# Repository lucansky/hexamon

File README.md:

# Hexamon.io - modular wireless beehive weighting system

Beehive monitoring - solves data acquisition from load cells placed under the beehives, data transport to server and data visualization for user.

## Architecture overview
### Master
Master unit consist of a Raspberry Pi with a CAN shield with RJ12 connector.
CAN shield is a board with SPI [MCP2515 CAN controller](http://ww1.microchip.com/downloads/en/DeviceDoc/21801d.pdf) and [SN65HVD23x](http://www.ti.com/lit/ds/symlink/sn65hvd230.pdf) CAN transceiver.

### Power management
The system is powered through a [18V solar panel](https://www.i4wifi.cz/Solarni-panely-1/Solarni-panely/Solarni-panel-GWL-Sunny-Poly-20-Wp-36-cells-MPPT-18V.html), charging [12V battery](https://www.gme.cz/oloveny-akumulator-shimastu-npg7-2-12-12v-7-2ah).
Enclosure with master unit has power management board for charging circuit with under-voltage protection, as well as 5V USB ports for output.

20W solar panel was selected for a prototype, due to it's ability to supply sufficient energy even during cloudy days for a Raspberry Pi.

### Bus unit
Under each beehive, assuming that whole chain of beehives is no longer than 100m, is placed platform with load cells for measuring the weight and bus unit in an enclosure. First beehive in chain contains Master and Bus unit at once.

Bus unit has STM32F042F6P6 in an TSSOP20 package with CAN transceiver and two RJ12 connectors for daisy-chaining to other bus units, as well as two holders for HX711 breakout boards. [Converters boards](https://www.aliexpress.com/item/10pcs-HX711-Weighing-Sensor-Dual-Channel-24-Bit-Precision-A-D-Module-Pressure-Sensor/32656264280.html) can be purchased through eBay or AliExpress.

Schematics & board design can be found in _boards_ directory.

### Weight acquisition
As an ADC with differential amplifier was selected chip HX711 integrated on a beakout board with all the necessary electronics around.

## Hardware
### Platform
Simple two-rail platform consists of three components:
* Load cell Zemic L6E or equivalent
* 2x Spacer
* 50x50mm 45cm L profile with drilled holes to match load-cell

Middle bars may be optional, depending on the situation:
* 2x Rectangle aluminium profile 25x15x3mm 25cm
* 2x Rectangle aluminium profile 25x30x3mm 25cm
These fit perfectly together. By drilling holes, pitch can be adjusted.

As the platform was not part of the project assignment, [contact me](mailto:adamlucansky@gmail.com) in case of interest.

### Load cells
During development, [Zemic L6E](https://www.zemiceurope.com/media/Documentation/L6E_Datasheet.pdf) were selected. For deployment, [L6G](https://www.zemiceurope.com/media/Documentation/L6G_Datasheet.pdf) are used. 

## Modularity
Several beehives can be chained together with a telephone cable with RJ12 jack through Bus unit under beehive, while master unit is sending captured data wirelessly to server through WiFi (3G/GSM modem option was tested and implemented, but is not further described, wvdial utility & whole ecosystem of linux drivers for modems make it diffucult for set-up).

## Software
### Master unit
Raspberry Pi 3 running Raspbian system, with an SPI overlay, provides can0 network interface which can be easily interfaced through linux socket. [Main program](https://github.com/lucansky/hexamond) is written in Haskell and is basically flipping frames received on CAN bus to HTTP requests to webservers where the data are further processed.

### Bus unit
[STM32F042](http://www.st.com/en/microcontrollers/stm32f0x2.html) MCU on board has 32kB of Flash memory and 6kB SRAM. Ivory language has been selected for generation of the C code, and Ivory framework as a hardware abstraction layer, message passing and RTOS interaction. Therefore whole project is 100% Haskell except the web. Firmware can be found [HERE](https://github.com/lucansky/hexamon-firmware).

### Web
Web interface provides charts for all sensors connected to the network as well as dashboard defined by user for aggregated statistics. Each setup requires separate instance of the web with database. Source code can be found [HERE](https://github.com/lucansky/hexamon-web)

# Results
System is deployed on a few beehives, needs a bit more tweaking (grounding of the metal platform with beehives, as interference is generated during thunderstorm) and better cable management.

__candump__ can be seed on monitor of the laptop of the deployment set. Battery is already charging from solar panel.

# Future work
Due to over-engineered solution, next iteration will be with [SIGFOX](https://en.wikipedia.org/wiki/Sigfox) - one module per beehive (just load cell cable connected to small box, 2xAA battery, optionally DS18B20 temperature sensor). Currently waiting for a [better signal coverage in Slovakia](http://www.simplecell.sk/pages/technologia_sigfox/), which is the reason SIGFOX was not considered from the beginning.

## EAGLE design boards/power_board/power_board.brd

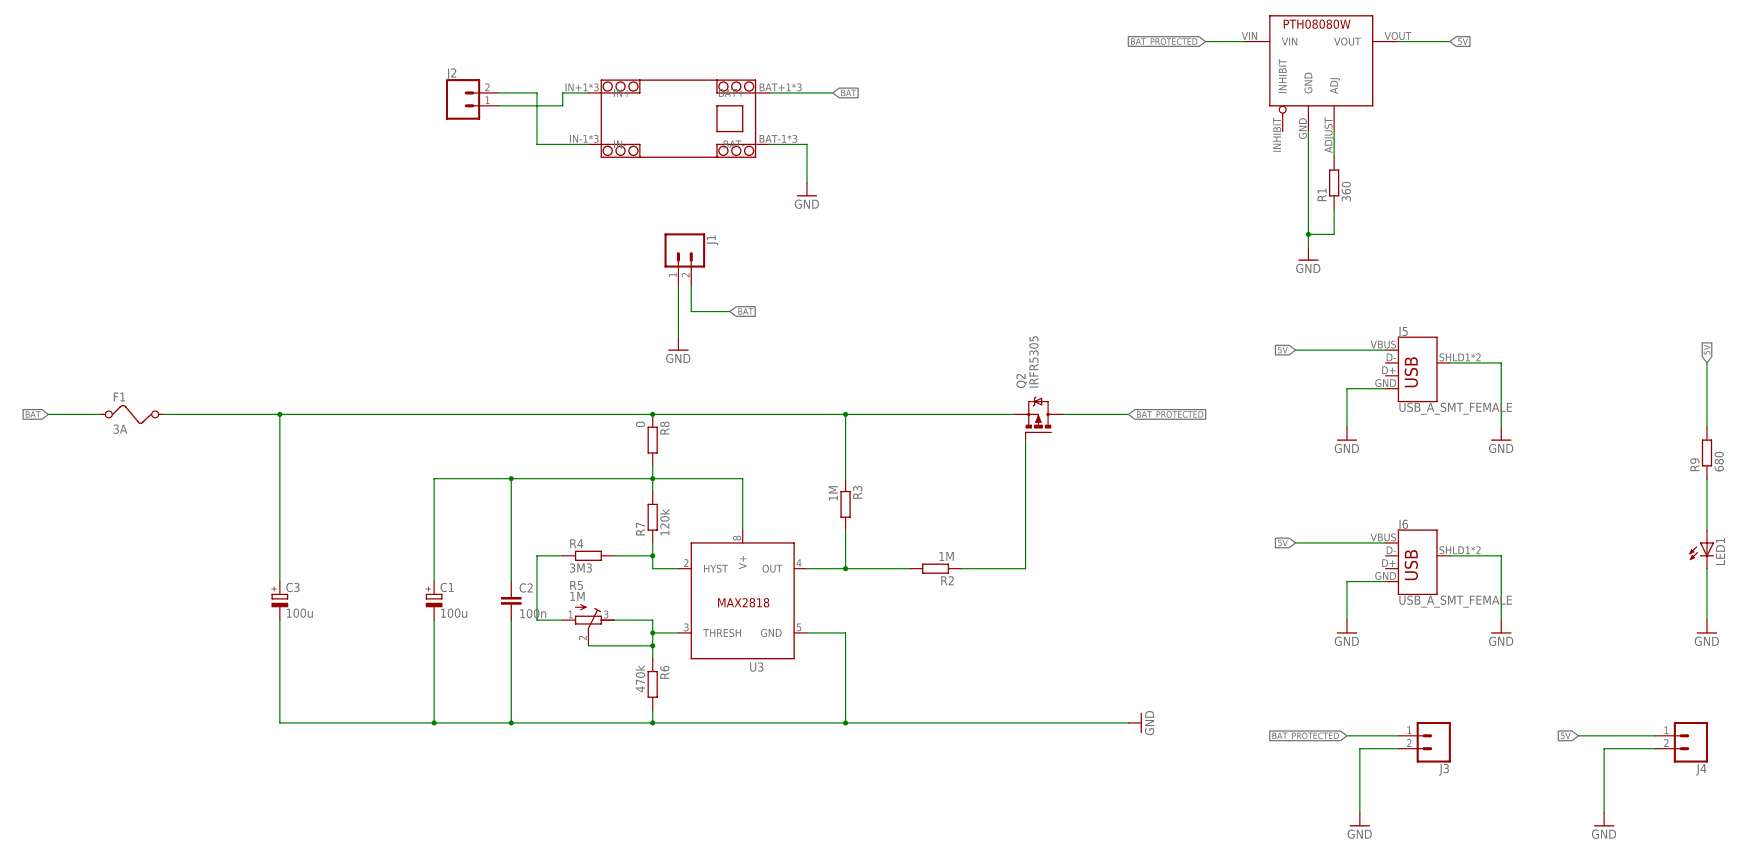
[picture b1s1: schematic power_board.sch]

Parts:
C1, C3: 100u; E3,5-8
C2: 100n; C1206
F1: 3A; FUSE
J1, J2, J4: CONN_025MM; SCREWTERMINAL-5MM-2
J3: CONN_02; 1X02
J5, J6: USB_A_SMT_FEMALE; USB-A-S-SILK-FEMALE
LED1: LED3MM
Q2: IRFR5305; D-PAK_TO252AA
R1: 360; R1206
R2, R3: 1M; R1206
R4: 3M3; R1206
R5: 1M; RTRIM64Y
R6: 470k; R1206
R7: 120k; R1206
R8: 0; R1206
R9: 680; R1206
U1: YZXSTUDIO_SOLARCHARGERDEFAULT; YZXSTUDIO_SOLARCHARGER
U2: PTH08080WPTH08080W; PTH08080W
U3: MAX2812MAX2812_SOIC8; SOIC127P600X175-8N

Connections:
5V: J4.1, J5.VBUS, J6.VBUS, R9.2, U2.VOUT
BAT: F1.1, J1.2, U1.BAT+1 (BAT+), U1.BAT+2 (BAT+), U1.BAT+3 (BAT+)
BAT_FUSED: C3.+, F1.2, Q2.3 (S), R3.1, R8.1
BAT_PROTECTED: J3.1, Q2.4 (D), U2.VIN
GND: C1.-, C2.2, C3.-, J1.1, J3.2, J4.2, J5.GND, J5.SHLD1 (SHIELD), J5.SHLD2 (SHIELD), J6.GND, J6.SHLD1 (SHIELD), J6.SHLD2 (SHIELD), LED1.K (C), R1.1, R6.2, U1.BAT-1 (BAT-), U1.BAT-2 (BAT-), U1.BAT-3 (BAT-), U2.GND, U3.5 (GND)
unnamed: J2.2, U1.IN-1 (IN-), U1.IN-2 (IN-), U1.IN-3 (IN-)
unnamed: J2.1, U1.IN+1 (IN+), U1.IN+2 (IN+), U1.IN+3 (IN+)
unnamed: R1.2, U2.ADJUST (ADJ)
unnamed: R5.2 (S), R5.3 (E), R6.1, U3.3 (THRESH)
unnamed: R2.2, R3.2, U3.4 (OUT)
unnamed: Q2.1 (G), R2.1
unnamed: C1.+, C2.1, R7.2, R8.2, U3.8 (V+)
unnamed: R4.2, R7.1, U3.2 (HYST)
unnamed: R4.1, R5.1 (A)
unnamed: LED1.A, R9.1

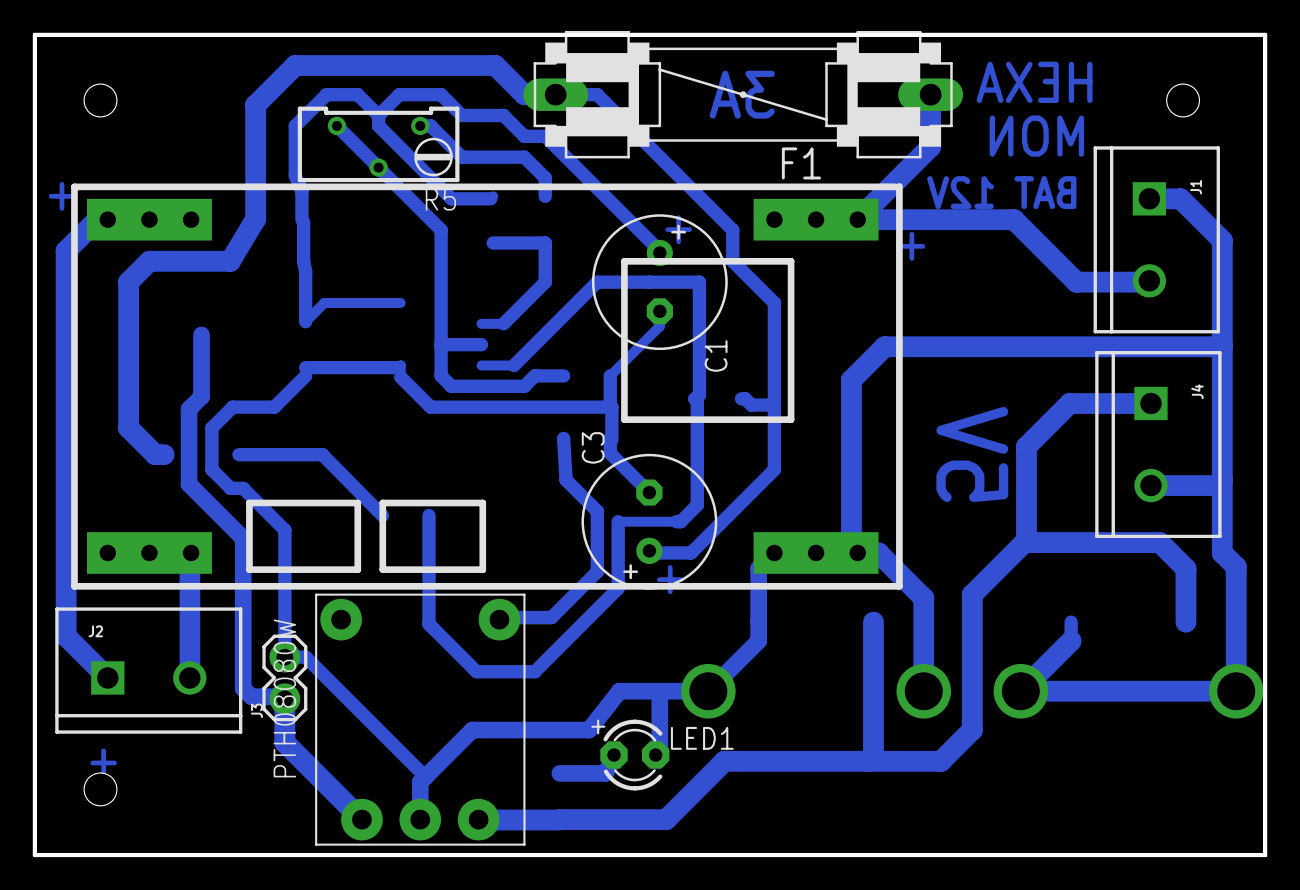
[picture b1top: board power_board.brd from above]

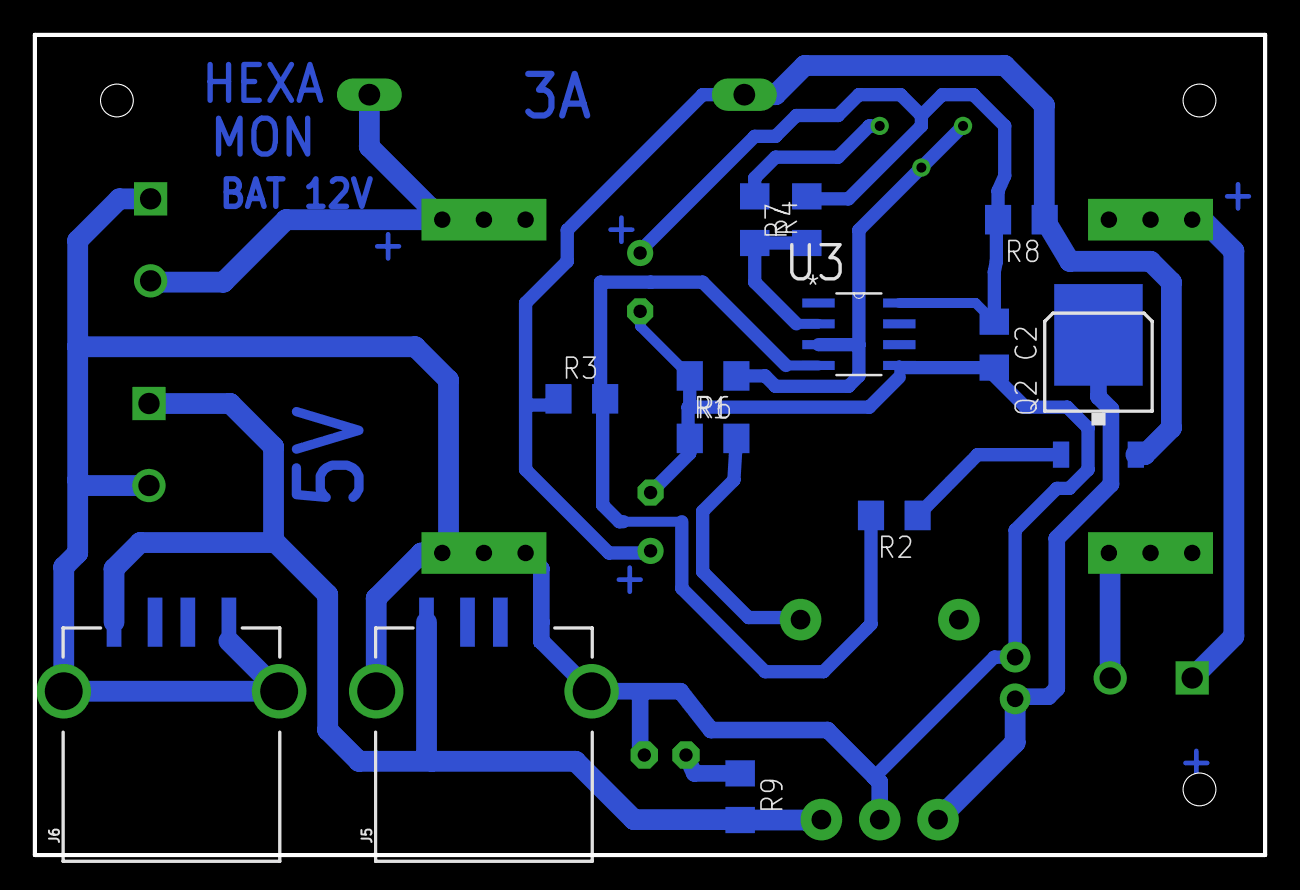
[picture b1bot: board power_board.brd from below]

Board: 2 copper layers, 75.0 x 50.0 mm, 24 parts (13 on the bottom side), 15 nets.

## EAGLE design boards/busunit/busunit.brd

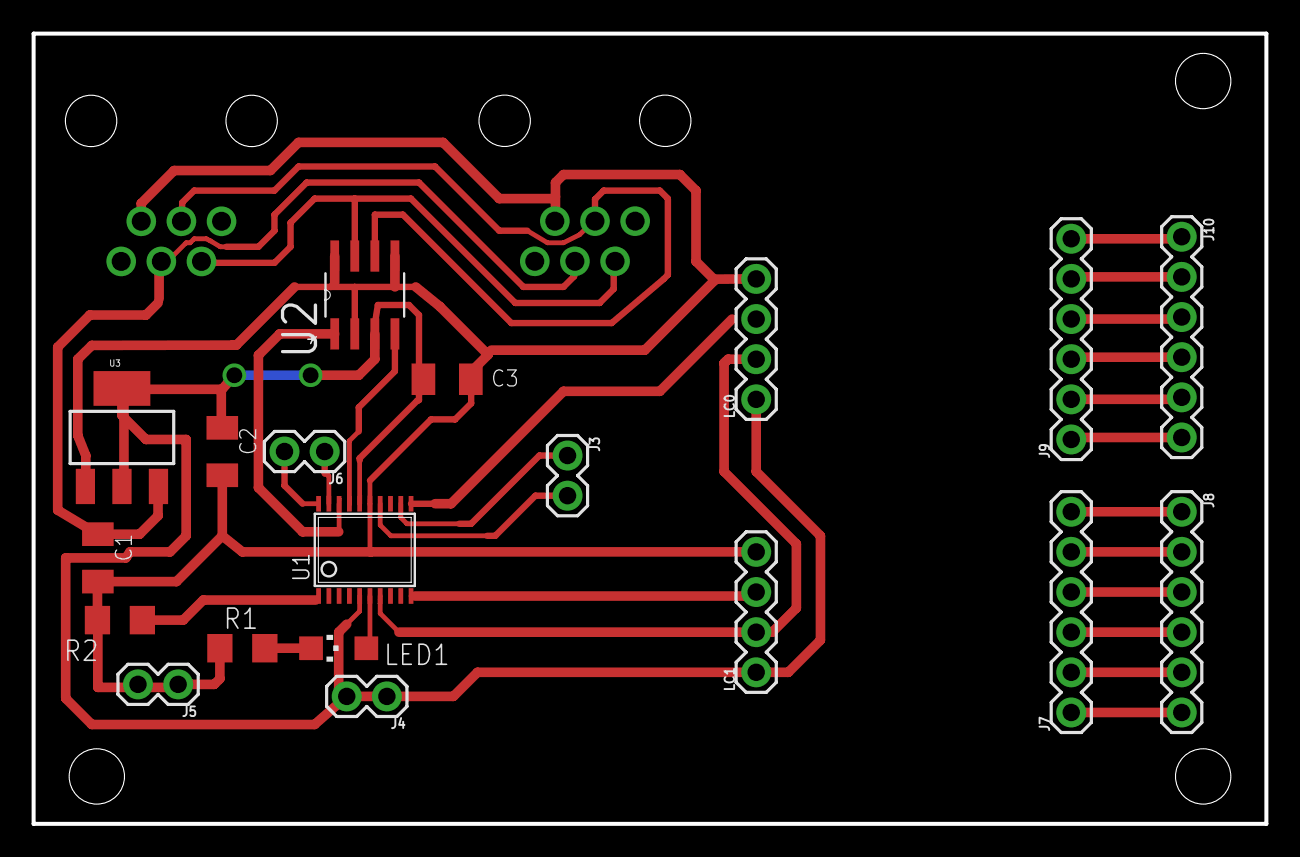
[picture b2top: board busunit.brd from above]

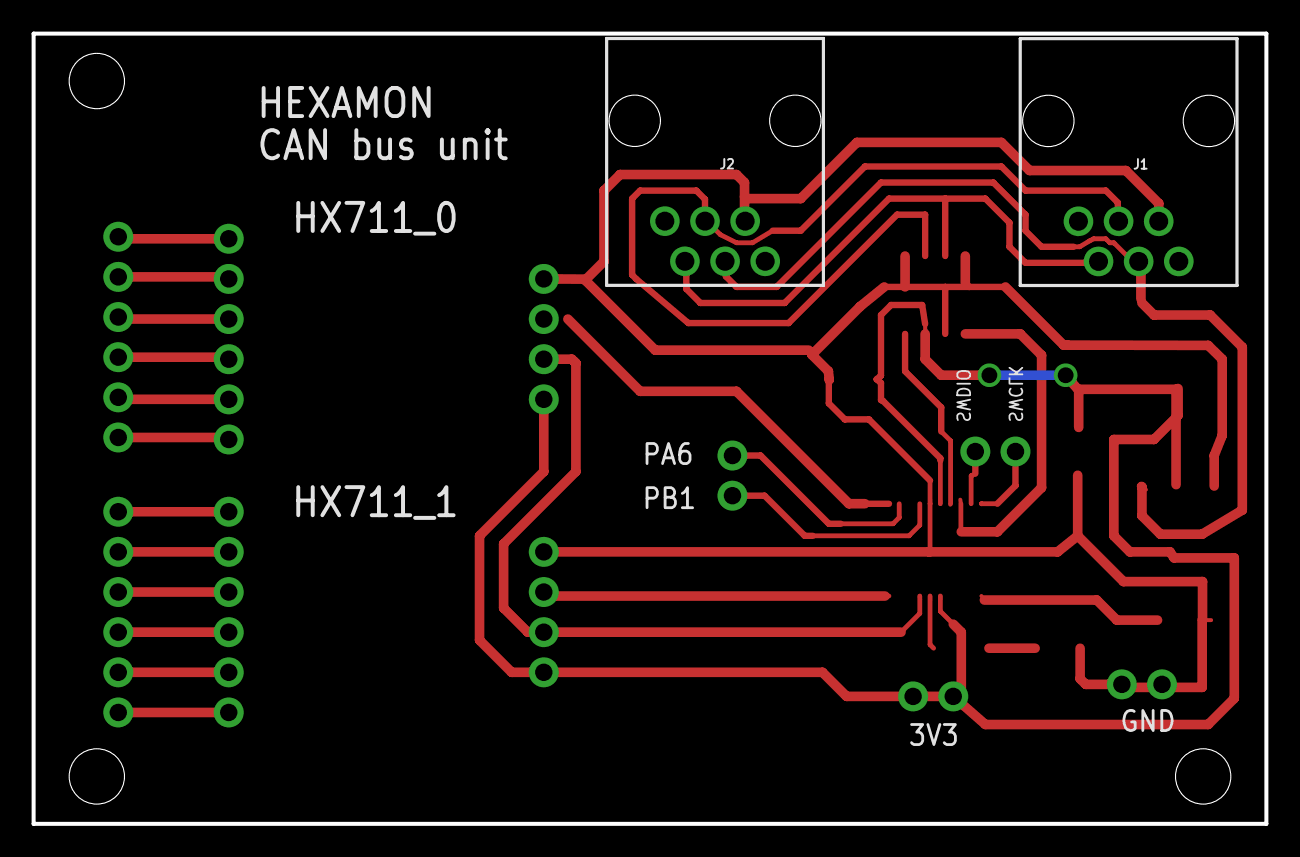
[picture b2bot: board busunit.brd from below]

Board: 2 copper layers, 78.0 x 50.0 mm, 21 parts (2 on the bottom side), 29 nets.

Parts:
C1: 0.1u; C1206K
C2, C3: 10u; C1206K
J1, J2: RJ11; RJ11-6
J3, J4, J5, J6: 1X02
J7, J8, J9, J10: 1X06
LC0, LC1: 1X04
LED1: CHIPLED_1206
R1: 470; R1206
R2: 10k; R1206
U1: STM32F030F4; TSSOP20
U2: SN65HVD233D; SOIC127P600X175-8N
U3: SOT223

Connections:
3.3V: C2.1, C3.1, J4.1, J4.2, LC0.1, LC1.1, U1.5, U1.16, U2.3, U3.2, U3.4
12V: C1.1, J1.3, J2.3, U3.3
CAN_H: J1.5, J2.5, U2.7
CAN_L: J1.4, J2.4, U2.6
CAN_RX: U1.17, U2.4
CAN_TX: U1.18, U2.1
GND: C1.2, C2.2, C3.2, J1.2, J2.2, J5.1, J5.2, LC0.4, LC1.4, R1.1, R2.2, U1.15, U2.2, U2.5, U2.8, U3.1
LED: LED1.A, U1.6
LOADCELL_CLK_SHARED: LC0.2, LC1.2, U1.7
LOADCELL_DT0: LC0.3, U1.11
LOADCELL_DT1: LC1.3, U1.10
unnamed: R2.1, U1.1
unnamed: LED1.C, R1.2
unnamed: J9.6, J10.1
unnamed: J9.5, J10.2
unnamed: J9.4, J10.3
unnamed: J9.3, J10.4
unnamed: J9.2, J10.5
unnamed: J9.1, J10.6
unnamed: J7.1, J8.6
unnamed: J7.2, J8.5
unnamed: J7.3, J8.4
unnamed: J7.4, J8.3
unnamed: J7.5, J8.2
unnamed: J7.6, J8.1
PA6: J3.1, U1.12
PB1: J3.2, U1.14
SWCLK: J6.2, U1.20
SWDIO: J6.1, U1.19

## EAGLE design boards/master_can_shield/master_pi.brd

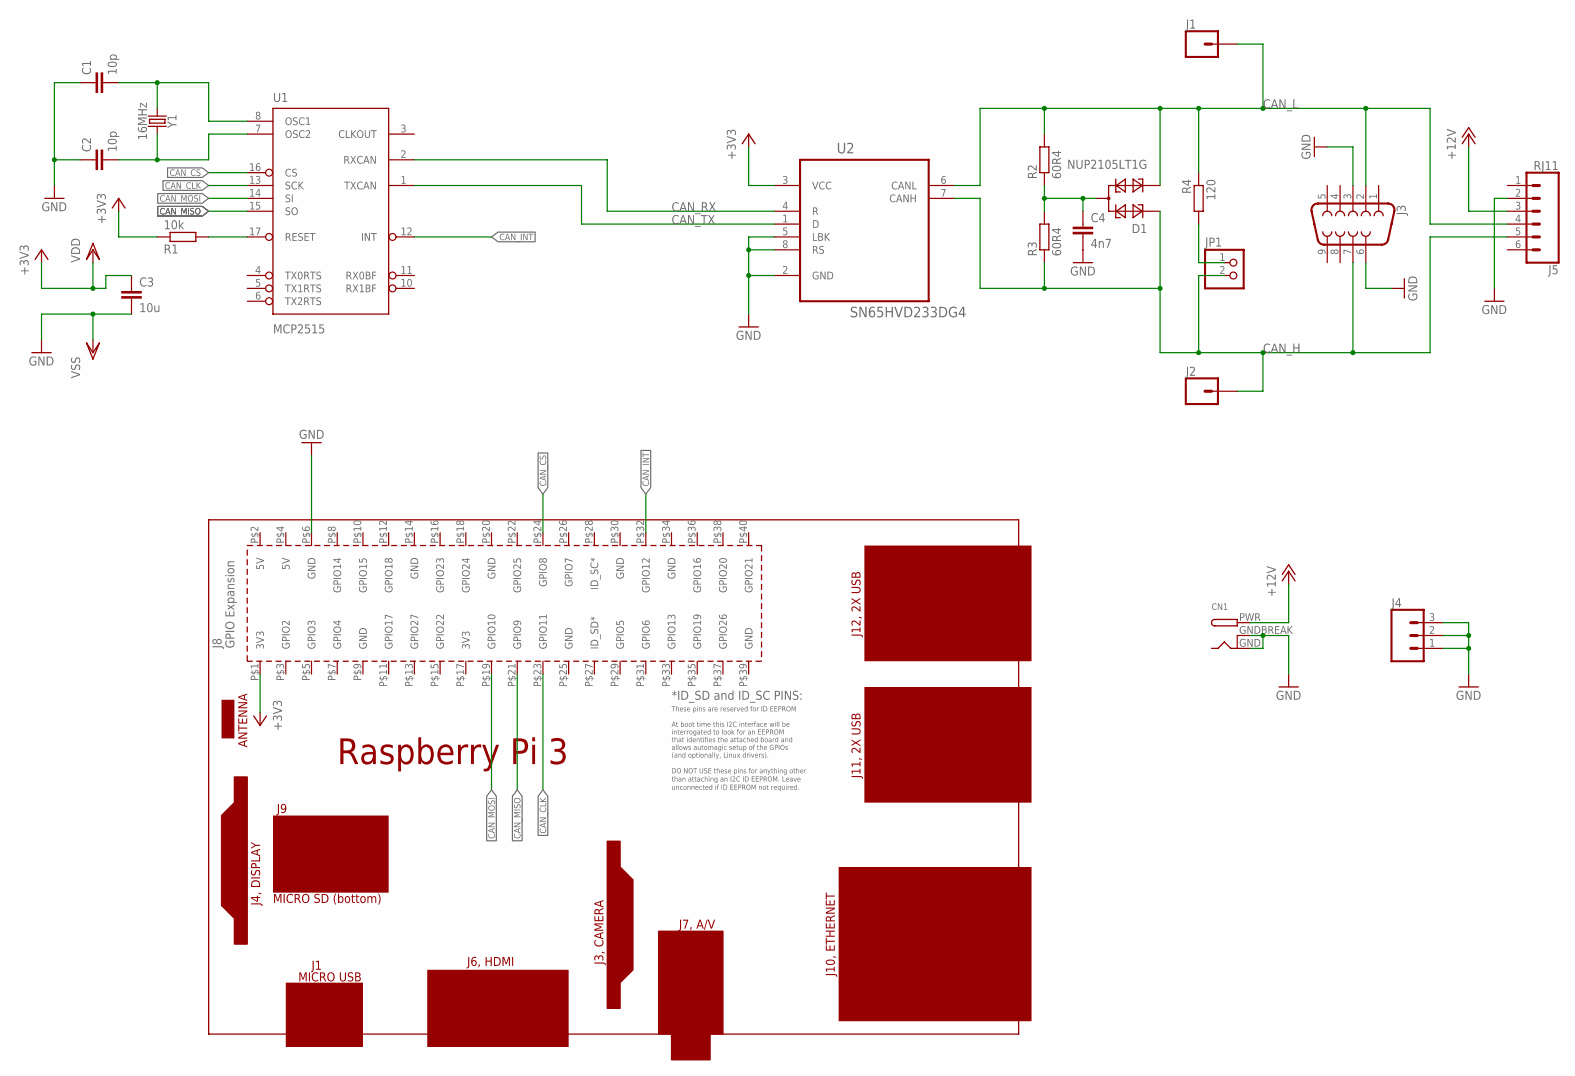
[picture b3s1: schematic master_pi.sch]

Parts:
C1, C2: 10p; C1206
C3: 10u; C1206
C4: 4n7; C1206
CN1: DCBARRELPTH; DCJACK_2MM_PTH
D1: NUP2105LT1G; SOT23
J1, J2: CONN_01; 1X01
J3: DB9FEMALE; DB9
J4: CONN_03; 1X03
J5: RJ11; RJ11-6
JP1: PINHD-1X2; 1X02
PCB1: RPI3
R1: 10k; R1206
R2, R3: 60R4; R1206
R4: 120; R1206
U1: MCP2515; SO18W
U2: SN65HVD233DG4; SOIC127P600X175-8N
Y1: 16MHz; HC49US

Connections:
+3V3: C3.1, PCB1.P$1 (3V3), R1.1, U1.18 (VDD), U2.3 (VCC)
+12V: CN1.PWR, J5.3
CAN_CLK: PCB1.P$23 (GPIO11), U1.13 (SCK)
CAN_CS: PCB1.P$24 (GPIO8), U1.16 (CS)
CAN_H: D1.1, J2.1, J3.7, J5.5, JP1.2, R3.1, U2.7 (CANH)
CAN_INT: PCB1.P$32 (GPIO12), U1.12 (INT)
CAN_L: D1.2, J1.1, J3.2, J5.4, R2.2, R4.1, U2.6 (CANL)
CAN_MISO: PCB1.P$21 (GPIO9), U1.15 (SO)
CAN_MOSI: PCB1.P$19 (GPIO10), U1.14 (SI)
CAN_RX: U1.2 (RXCAN), U2.4 (R)
CAN_TX: U1.1 (TXCAN), U2.1 (D)
GND: C1.1, C2.1, C3.2, C4.2, CN1.GND, CN1.GNDBREAK, J3.3, J3.6, J4.1, J4.2, J4.3, J5.2, PCB1.P$6 (GND), U1.9 (VSS), U2.2 (GND), U2.5 (LBK), U2.8 (RS)
unnamed: R1.2, U1.17 (RESET)
unnamed: C4.1, D1.3, R2.1, R3.2
unnamed: C1.2, U1.8 (OSC1), Y1.1
unnamed: C2.2, U1.7 (OSC2), Y1.2
unnamed: JP1.1, R4.2

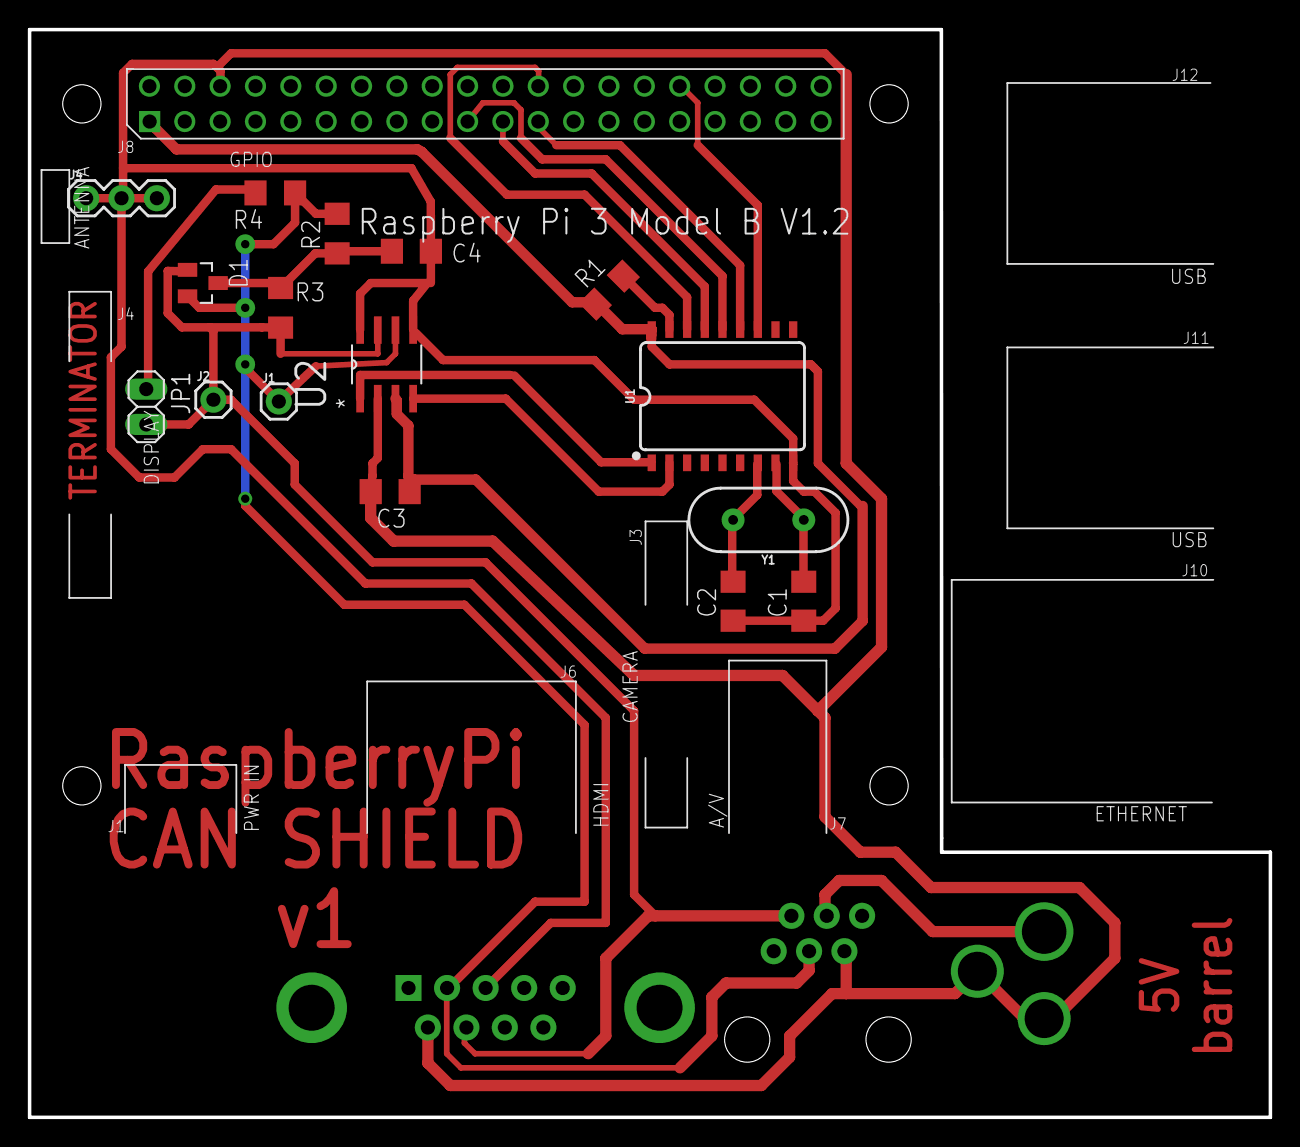
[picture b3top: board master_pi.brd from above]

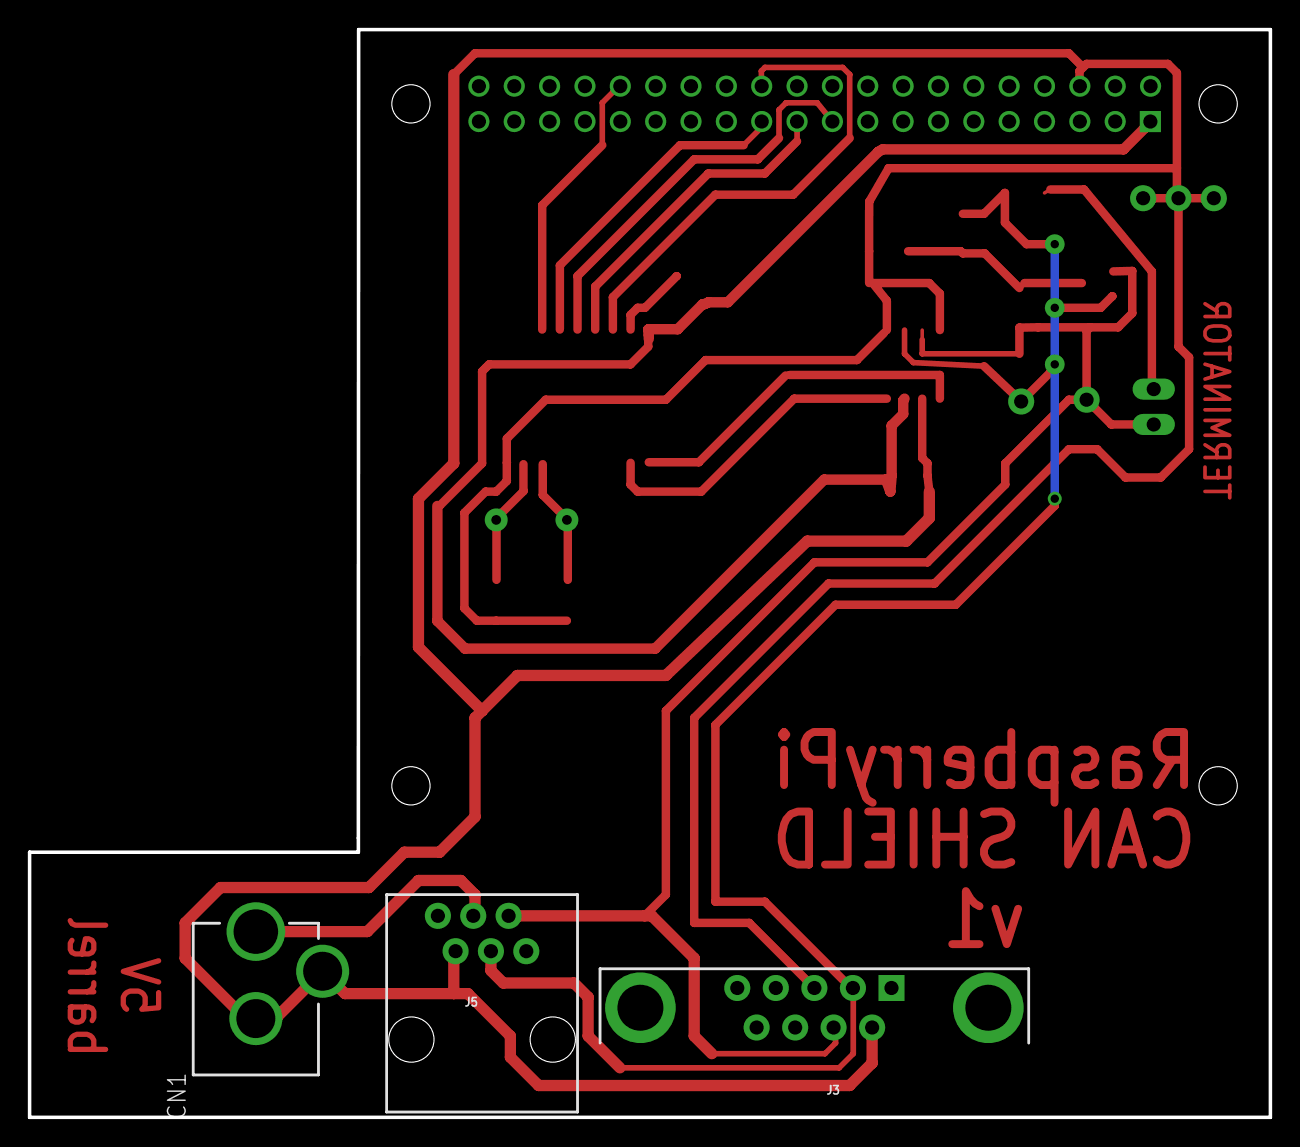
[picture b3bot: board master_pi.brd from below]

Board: 2 copper layers, 89.2 x 78.2 mm, 20 parts (3 on the bottom side), 17 nets.

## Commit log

2017-04-24 Added images
2017-04-24 Added image files
2017-04-30 Nested images
2017-04-30 Going public with boards
2017-05-01 Moved some labels to bottom layer in busunit, exported libraries.
2017-05-01 Updated links in README.md
2017-05-16 Minor modifications, images of board & schema included
2017-05-21 Added links to README
2017-05-21 Addded new images, rescaled previous
2017-05-21 Moved images to subdir.
2017-05-21 Better descriptions

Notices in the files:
parts and their libraries:
SparkFun-Connectors: Licensing: Creative Commons ShareAlike 4.0 International - https://creativecommons.org/licenses/by-sa/4.0
